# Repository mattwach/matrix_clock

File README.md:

# matrix_clock
> "I DON’T EVEN SEE THE CODE ANYMORE" - The Matrix.  

Shown above is a clock that presents the current time on an 64x32 RGB LED
matrix.  The clock has other selectable modes, including a view that includes
the numbers:

and some other selectable views:

Although the images above give you a basic idea, they can't show you the
dynamic range of the LED or the visual impression of 200 FPS animations,

The project's firmware is designed to easily incorporate support for other
hardware configurations.  Included is a 8x8 "Dotstar" matrix version that was my
first version:

*This document* focuses on the newer 62x32-based model, which I prefer.  If you
want to learn more details on the 8x8 build, I have a separate document
for it [here](README_dotstar_8x8.md).

In the upcoming sections, I explain how I built the clock.  I also
explain how to modify the design in different ways.

# Parts List

You can of course modify the design to use different ones.  Prices are "at time
of writing":

   * Microcontroller: [Raspberry PI Pico ($4)](https://www.adafruit.com/product/4864)
   * [LED Matrix 62x32: ($30)](https://www.amazon.com/waveshare-Displaying-Animation-Adjustable-Brightness/dp/B0B3W1PFY6)
     Note there are many vendors of this display - I assume they have similar
     interfaces.
   * Clock: [DS3231-based RTC module ($4)](https://www.amazon.com/HiLetgo-AT24C32-Arduino-Without-Battery/dp/B00LX3V7F0).
     This part is optional-but-recommended. The firmware can be built to use the
     Pi Pico clock libraries but you will lose battery backup and the time
     will drift more. 
   * Buttons: I used [2 6mm push buttons for control (<$1)](https://www.amazon.com/WOWOONE-12x12x7-3-Tactile-Momentary-Assortment/dp/B08JLWTQ3C)
     and one 6x3 SMD button for optional reset capability.
   * Connectors:
     * I used one 8x2 2.54 pitch male pin header to interface the Pico PCB with
       the matrix (using the usually-included interface cable)
     * I used a 2x1 angled 2.54 pitch pin header for connecting the LED to the
       PCB.
     * I used a 3x1 angled 2.54 pitch pin header for connecting the buttons to
       the PCB
   * I used a 220uF capacitor to reduce 5V noise.  Somewhat larger or smaller
     values should also work fine.
   * Circuit board for assembling components.
     * There are many options.  I ended up ordering a PCB from
       http://oshpark.com for the main board because my PCB layout needs a
       two-layer board.  I could have wired it up on perf board, but the large
       number of pin connections would have make it difficult to get a clean
       result.
     * There is a separate PCB for the buttons.  This board is very simple so
       any build technique should be straight-forward.  I used my CNC
       machine to cut a board within an hour.  If you order a main board, you
       might opt to bundle the button pcb with the order. 

Optional:

The LED display can pull over 3A if all LEDs are set to white.  The firmware I
wrote never does this and needs about 100-300 mA for most of the modes
(as-measured with a multimeter).  Thus I'm using the Pi Pico's VDD pin, which is
directly connected to USB power.  This connection should be limited to 500 mA or
less, thus I added the following electronic components to enforce the current
limit:

   * NCP380 current limiting IC
   * Two additional 1uf capacitors for stability.  I am using SMD but ceramic
     through-hole are also an option.

My hardware has this current protection but it has never activated outside of
testing thus one might argue that it's not needed.  If you plan to make your own
display modes, I suggest including the protection.

# Reading the clock

How can the clock be read when no numbers are shown?  By noting the colors and
speed of the particles.  Here is my color mapping for each number, as shown in
the time setting interface:

> Colors are defined in [src/colors.c](src/colors.c) if you would like to edit
> them.

# Feature Overview

This is a quick tour of the built in-features

## Power On

When you plug in the clock via any USB power source you will get a matrix clock
display that indicates the current time as-reported by the RTC clock hardware.

## Setting the Time

The clock has two buttons on it's side: "set" and "increment". Pressing "set"
goes into time change mode where you can use "set" and "increment" to change
each time digit.

> You can also set the clock via the USB connection.

## Changing the Display Mode

If you press the "increment" button while the matrix is showing, the clock will
cycle through display modes.  Currently defined modes include:

* **Simple** Shows the time with no animations.  The color of the time
  changes throughout the day to approximate a sunrise/daytime/sunset color
  temperature.
* **Matrix With Numbers** The default
* **Matrix Only** For those who want a challenge
* **Bounce** Particles bounce around the numbers. 
* **Number Cascade** Digits fall from the top of the display to the bottom.  The
  size and speed of the digit represent the place in the time (hours vs
  minutes).
* **Waveform** Waveforms progress from the bottom of the display to the top at
  different speeds based on the time digit.
* **Drops** A water droplet effect appears behind the numbers.
* **Off -**  Useful if you want a darkened room.

Each display mode uses color as described earlier to accent the current time.

## Console Configuration

If you plug the clock into a computer, you can run a terminal emulator program
to access many additional settings.  In Linux, I use the "minicom" terminal
emulator and my command looks like this:

```bash
minicom -b 115200 -P /dev/ttyUSB0
```

> The serial device (`/dev/ttyUSB0`) can vary between computers and operating
> systems. 

Once started, you will see something like this:

> By default, `minicom` turns on local echo, making my typed characters appear
> twice.  `minicom` allows this to be turned off with `ctrl-a e`.

Type `help` or `?` for help.

# Build Instructions

## Electronics

Here is the schematic for the 64x32 version:

Here is a description on major components and their purpose:

  - **Pi Pico**: This is the main controller
  - **RTC (Real Time Clock, Optional)**: This provides time to the Pico via an I2C connection.
    You could use alternate clock hardware as described in a later section.  In
    terms of the I2C connection, note that the RTC clock is powered by 3.3V
    instead of the specified 5V.  This is the easiest way to make the clock
    compatible with the 3.3V maximum voltage of the PI Pico.  If your RTC really
    does need 5V, there are solutions but the details are not the focus of this
    document.  Thus I suggest doing a Google search for "3.3 to 5V I2C" to learn
    more.
  - **64x32 matrix**: This is also a 5V part and is connected to the 5V VDD of the
    Pico, allowing ~500mA to be safely consumed by the panel.  The Pico is
    directly connected and will deliver 0-3.3V *signals* to the panel.  Unlike
    I2C for the RTC clock, the LED pins are high impedance inputs with no pullup
    thus there is no hardware risk in connecting them directly to the Pico.  The
    main risk is that the LED panel will not accept 3.3V as a legitimate "high"
    signal and thus it wont work.  For my panel 3.3V was accepted without a
    problem thus no level converters were needed.  I suspect this is the common
    scenario with these panels.
  - **100 uF-470 uF capacitor**.  The actual value is not important other than
    "big".  The purpose of the capacitor is to support the power requirements of
    the LED, which can be a "noisy" load, needing near zero current one moment
    and several hundred mA the next.
  - **Buttons**.  Select, increment and reset as described earlier.
  - **NCP380 current limiting chip (optional)**.  This chip provides insurance for
    the case where you one day decide to change the firmware to light up many
    LEDs and draw too much current.  If you really want to do support high
    current draw, you'll need to rework the power design so that the LED panel
    can be directly powered from a capable (3A+) source instead of VDD on the
    Pico.
    
> VDD on the Pico is a direct passthrough to the USB power so it's the
> USB regulator (wall adapter or computer) and the PCB traces of the Pico that are
> the main power bottlenecks.

> If you don't us use the NCP380, simply connect the Pico VDD pin directly to the LED.
> Keep the 100u capacitor for noise purposes.

In terms of layout, here is the KiCAD layout for the schematic above (with
ground plane hidden):

and here is a photo of the completed PCB.  Note that the capacitor can't be seen
because it is on the backside of the board:

As for the buttons, here is the simple KiCAD layout:

and the finished board that I cut out with my CNC machine (just using a perf
board would also work fine):

## Firmware

> TLDR: If you don't want to build the firmware (`matrix_clock_led_64x32.uf2`) 
yourself, I have a couple of precompiled versions under the
[firmware](firmware) directory.

Source files (written in C) are  provided in the [src/](src) directory.  If you
have never built PI Pico firmware before, run through the official [Getting
started with the Raspberry Pi
PICO](https://datasheets.raspberrypi.com/pico/getting-started-with-pico.pdf)
documentation first to get the needed tools up-and-running on your system.

The instructions for building the clock firmware are the same as the guide
linked above, but I created a small/simple [bootstrap.sh](src/bootstrap.sh)
script to lessen the number to needed steps:

```bash
./bootstrap.sh 
cd build/
make -j
```

I encourage you to view the contents of [bootstrap.sh](src/bootstrap.sh)
  yourself instead of blindly running it.  You'll see something like this:

```bash
$ cat bootstrap.sh 
#!/bin/bash

if [ ! -f pico_uart_console/CMakeLists.txt ]; then
  git submodule init
  git submodule update
fi

rm -rf build
mkdir build
cd build
cmake ..
```

> If building under Windows, you may opt to run the DOS-equivalent commands
> contained within `bootstrap.sh` manually.  The good news is that there
> are only a few commands to run.

The two major things done here are getting some dependencies (git submodules)
and setting up a new build environment under `build/`

If all went well above, you will have a `src/build/matrix_clock.uf2` file
available to load onto a PI Pico.  Note that
`firmware/matrix_clock_led_64x32.uf2` will not be changed.

# Hardware build

The hardware build is fairly minimalistic, solving the given problems:

  * Securing the PI Pico, RTC hardware and buttons at the bottom of the panel
  * Keeping the connection cables constrained so the clock can mount flat on a
    wall
  * Providing a wall mount

I solved all of these problem by creating a couple of 3D models and printing them out.
I used OpenSCAD for the modeling.

This model is located at
[case/led_matrix_64x32/led_matrix_64x32.scad](case/led_matrix_64x32/led_matrix_64x32.scad).
It can be modified with any text editor and viewed in the free
[OpenSCAD](http://openscad.org) software.

If you don't want to mess around with OpenSCAD, I also have the models available
for direct download at
[case/led_matrix_64x32/export](case/led_matrix_64x32/export).  These are .3mf
files (the successor to .stl format) that most modern slicer programs can
directly load.

To assemble, I used M2 bolts to attach the buttons to the bottom, 6mm long I
think but something in that area should be fine.  I used M3 bolts (around
12-16mm) to attach the 3D printed parts to the led matrix.

The PCB settles into a custom slot in the bottom 3d part (see the grooves in the
red image above) and is held in place with no bolts required, just make sure
it's in the proper position before tightening the frame bolts.

The hex matrixes on the back hold the power and led interface cables within the
unit so that it will mount flush on the wall.  A guide and slot is provided for
wall hanging the unit.

# Customization Guide

This part of the documentation points you in the right direction if you want to
modify the project.  This entire section should be consider optional and more
advanced than others.

## Using Different LED Hardware

The file [src/led_matrix.h](src/led_matrix.h), contains the interface your
hardware driver will be called with.
[src/led_matrix_62x32.c](src/led_matrix_64x32.c) implements it for the 64x32 LED
hardware.  There is also a [src/led_matrix_dotstar.c](src/led_matrix_dotstar.c)
file which is used *instead* when building the dotstar version.  To add
additional hardware support, create a new `.c` file (for example
`src/led_matrix_neopixel.c`) and change [src/CMakeLists.txt](src/CMakeLists.txt)
to point to your new file.c`.  The main function you'll be implementing is:

```c
#define LED_MATRIX_WIDTH 8
#define LED_MATRIX_HEIGHT 8

// render the matrix.
// data is of the form 0xIIRRGGBB where
// II -> Intensity (brightness)
// RR -> Red
// GG -> Green
// BB -> Blue
//
// Values are 0-255
// format is horizontal rows.  The first pixel
// sent is the southwest corner of the matrix.
void led_matrix_render(uint32_t* data);
```

Again, look at [src/led_matrix_dotstar.c](src/led_matrix_dotstar.c) for a
straight-forward implementation of `led_matrix_render`.

## Using Different Clock Hardware

Instead of an RTC, you might want to go with a radio-based clock, a GPS clock,
or [keeping the time with the Pi
Pico](https://raspberrypi.github.io/pico-sdk-doxygen/group__hardware__rtc.html).

> The PICO SDK provides time functions but you'll lose battery backup and
accuracy is not as good as a real RTC.

[src/clock.h](src/clock.h) gives the interface:

```c
// gets the current time in HHMM format (0000 - 2359)
// For example, if 1354 is returned, the time is 13:54 (or
// 1:34 PM if you prefer)
uint16_t clock_get_time();

// Sets the time.  For example: time_hhmm = 1234 would set the
// time to 12:34.  Note that 24h time is always used so 1234
// is 12:34 PM and 0034 is 12:34 AM.
void clock_set_time(uint16_t time_hhmm);
```

and [src/clock_ds3231.c](src/clock_d23231.c) gives a concrete implementation for
the RTC module.  The file [src/clock_pico_internal.c](src/clock_pico_internal.c)
provides an implementation that does not need RTC hardware.  It can be selected
in [src/CMakeLists.txt](src/CMakeLists.txt).

## Adding / Changing Display Modes

There are two files and one directory to consider.  The first file is
[src/clock_render.c](src/clock_render.c).  Specifically, this section:

```c
  struct DisplayMode display_modes[] = {
    {"matrix_with_numbers", matrix_with_numbers_render},  // This entry will be the default power-on mode
    {"matrix", matrix_render},
    {"bounce", bounce_render},
    {"number_cascade", number_cascade_hires_render},
    {"waveform", waveform_render},
    {"drops", drops_render},
    {"off", blank_render},  // always put this entry at the end of the list
  };
```

This section lists the display modes, names them and provides a function pointer
to each one.  If you were to remove a line from this array, or reorder the
lines, you would see the corresponding change when you build/load new firmware.
In order for the function pointers to have any meaning, you'll need to include
the corresponding files:

```c
#include "render/matrix_with_numbers.h"
#include "render/matrix.h"
#include "render/bounce.h"
...
```

Note that, by convention, all rendering functions are defined in the
[src/render](src/render) directory.  Here is an example
[src/render/blank.c](src/render/blank.c):

```c
void blank_render(
    uint32_t* led,
    uint32_t frame_index,
    uint16_t time_hhmm,
    const struct ClockSettings* settings) {
  memset(
    led,
    0,
    LED_MATRIX_WIDTH * LED_MATRIX_HEIGHT * sizeof(uint32_t));
}
```

This simple function simply clears the `led` array to zero which effectively
turns off the display.

The `time_hhmm` provides the time as an integer.  For example, 1:45 AM would be
represented as `0145` and 1:45 PM would be represented as `1345`.

The `frame_index` parameter can be useful for initialization.  It is always set
to `0` when the display mode is made active.

The `settings` structure has several potentially-useful fields but especially
useful is getting the user preference for LED brightness:

```c
  const uint8_t br = brightness_step_to_brightness(settings);
```

This value (0-255), would then be used as a baseline brightness when turning on
LEDs in `led`

## Changing the Console

The file `src/clock_settings.c` contains all of the commands available to the
USB shell.  Adding your own is straight-forward but I suggest skimming through
https://github.com/mattwach/pico_uart_console to get up-to-speed on how the
console works first.

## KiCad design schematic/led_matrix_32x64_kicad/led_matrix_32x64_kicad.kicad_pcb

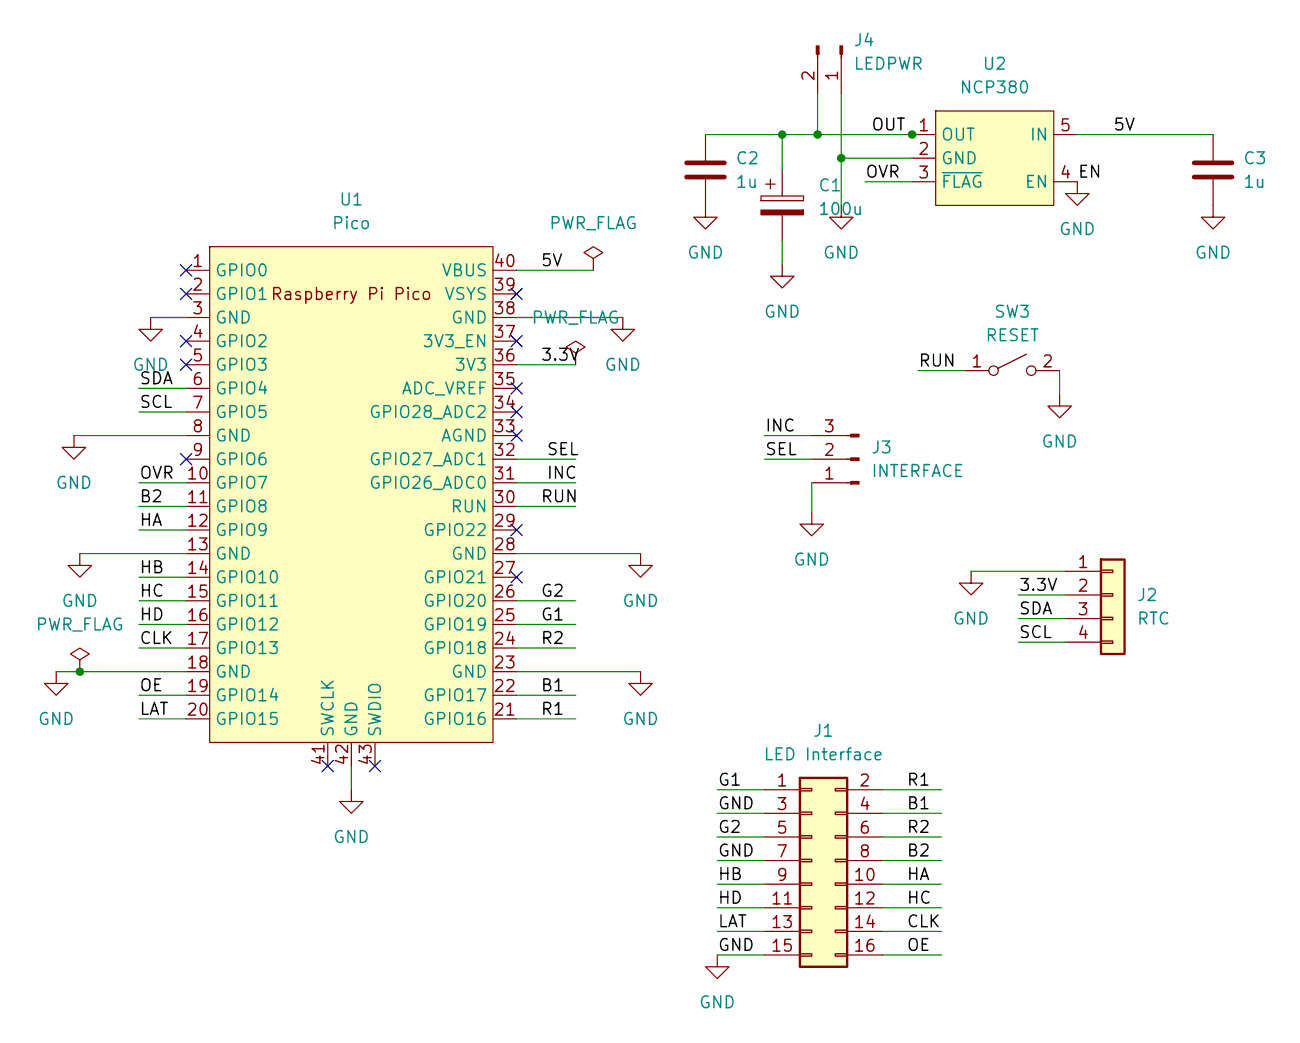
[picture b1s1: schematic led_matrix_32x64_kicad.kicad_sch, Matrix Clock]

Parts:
C1: 100u; CP_Radial_D6.3mm_P2.50mm
C2, C3: 1u; C_0805_2012Metric_Pad1.18x1.45mm_HandSolder
J1: LED Interface; PinHeader_2x08_P2.54mm_Vertical
J2: RTC; PinHeader_1x04_P2.54mm_Vertical
J3: INTERFACE; PinHeader_1x03_P2.54mm_Horizontal
J4: LEDPWR; PinHeader_1x02_P2.54mm_Horizontal
SW3: RESET; SMD_Button_6mm_3_5mm
U1: Pico; RPi_Pico_SMD_TH
U2: NCP380; TSOP-5_1.65x3.05mm_P0.95mm

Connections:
/3.3V: J2.2, U1.36 (3V3)
/5V: C3.1, U1.40 (VBUS), U2.5 (IN)
/B1: J1.4, U1.22 (GPIO17)
/B2: J1.8, U1.11 (GPIO8)
/CLK: J1.14, U1.17 (GPIO13)
/G1: J1.1, U1.25 (GPIO19)
/G2: J1.5, U1.26 (GPIO20)
/HA: J1.10, U1.12 (GPIO9)
/HB: J1.9, U1.14 (GPIO10)
/HC: J1.12, U1.15 (GPIO11)
/HD: J1.11, U1.16 (GPIO12)
/INC: J3.3, U1.31 (GPIO26_ADC0)
/LAT: J1.13, U1.20 (GPIO15)
/OE: J1.16, U1.19 (GPIO14)
/OUT: C1.1, C2.1, J4.2, U2.1 (OUT)
/OVR: U1.10 (GPIO7), U2.3 (~FLAG)
/R1: J1.2, U1.21 (GPIO16)
/R2: J1.6, U1.24 (GPIO18)
/RUN: SW3.1 (A), U1.30 (RUN)
/SCL: J2.4, U1.7 (GPIO5)
/SDA: J2.3, U1.6 (GPIO4)
/SEL: J3.2, U1.32 (GPIO27_ADC1)

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
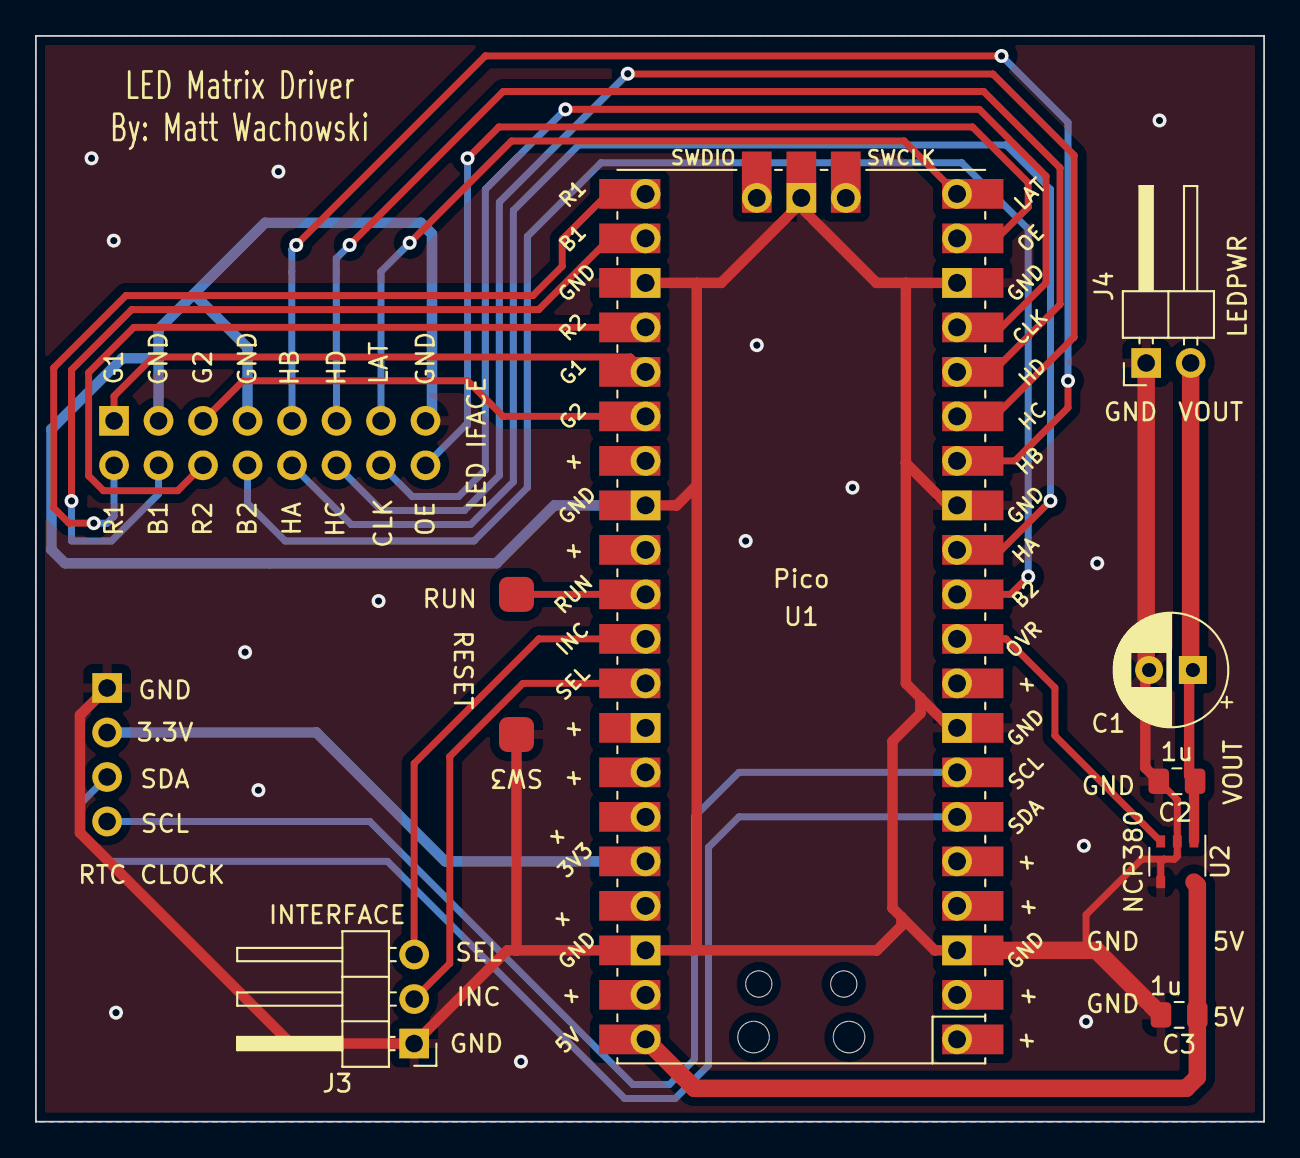
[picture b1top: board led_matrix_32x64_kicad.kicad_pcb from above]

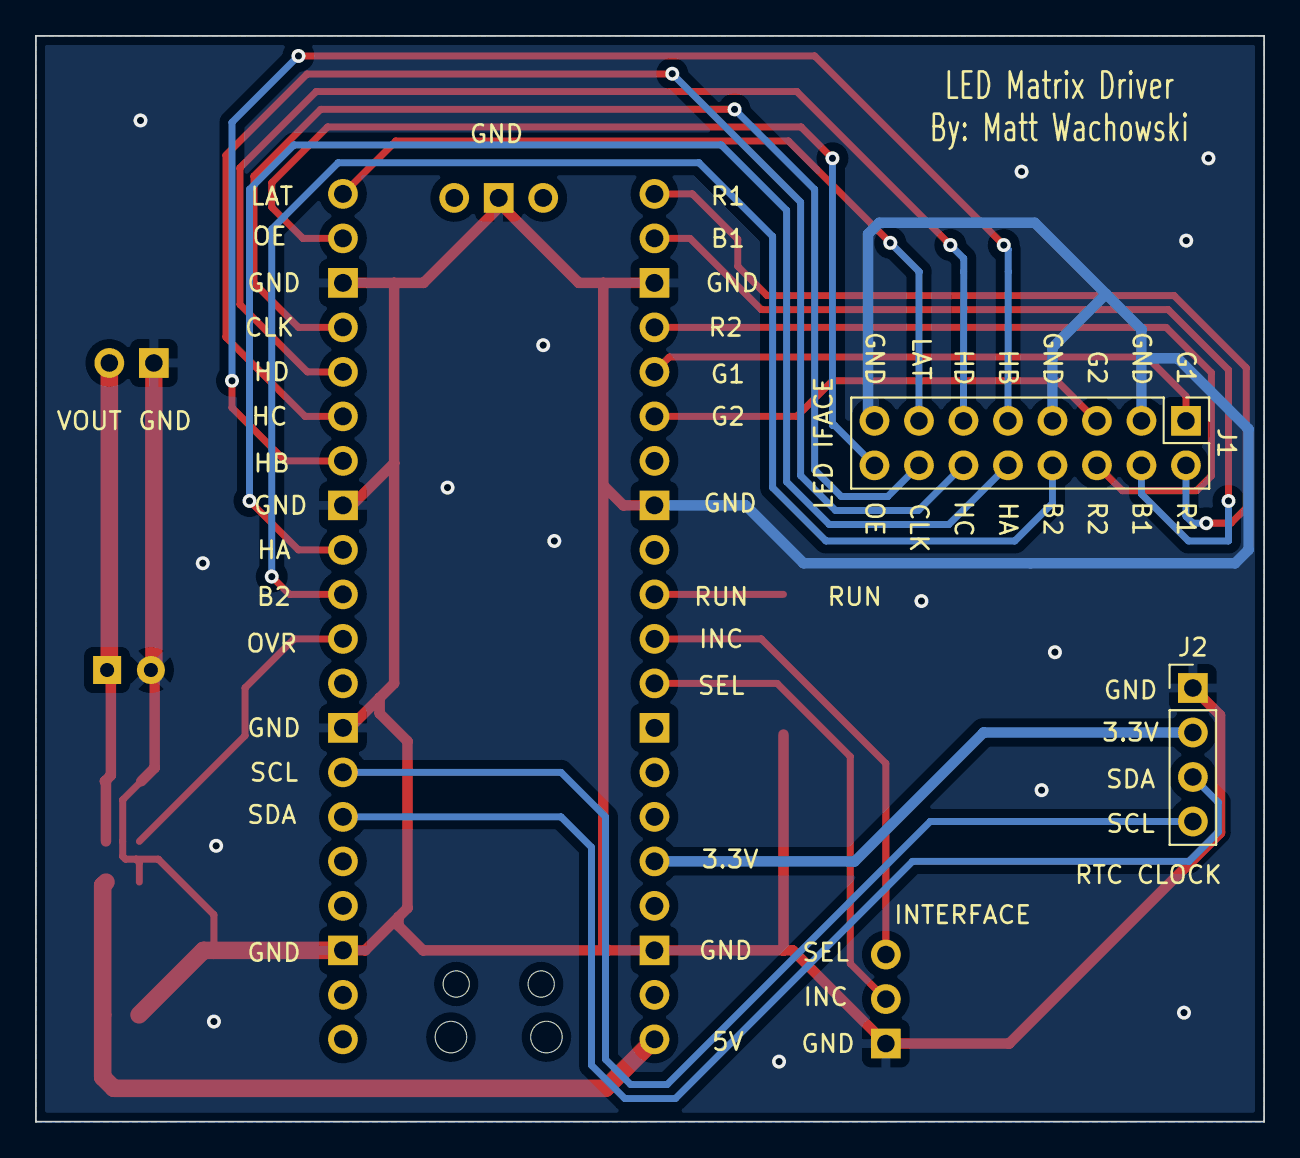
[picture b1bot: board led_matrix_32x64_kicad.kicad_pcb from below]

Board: 2 copper layers, 70.1 x 62.0 mm, 10 parts (2 on the bottom side), 23 nets.

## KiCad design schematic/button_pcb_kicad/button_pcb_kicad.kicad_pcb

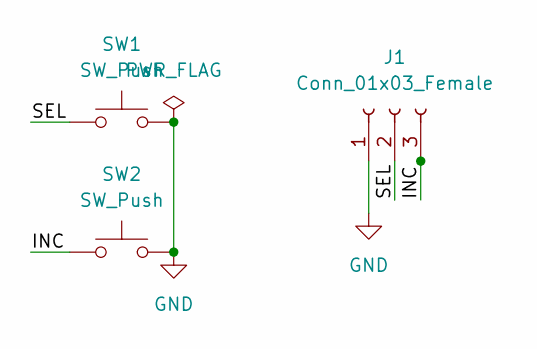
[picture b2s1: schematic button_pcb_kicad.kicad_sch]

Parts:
J1: Conn_01x03_Female; SMD_Pad_1x03_2mm
SW1, SW2: SW_Push; SW_PUSH_6mm_H4.3mm

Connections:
/INC: J1.3, SW2.1
/SEL: J1.2, SW1.1
GND: J1.1, SW1.2, SW2.2

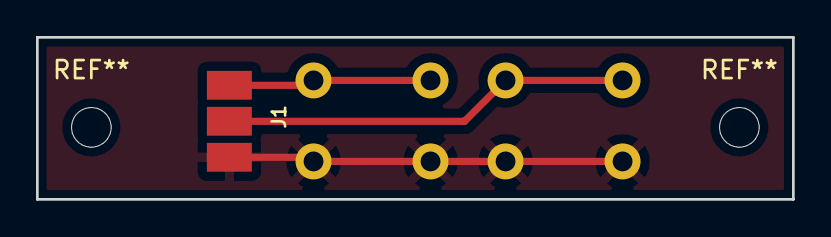
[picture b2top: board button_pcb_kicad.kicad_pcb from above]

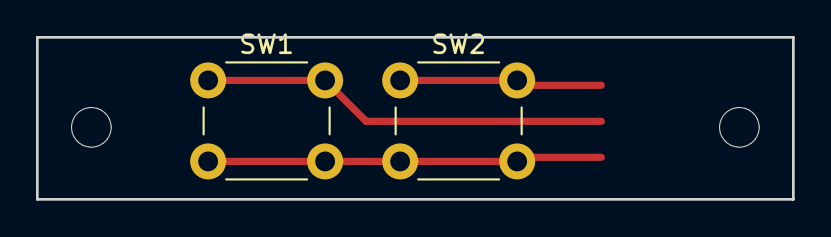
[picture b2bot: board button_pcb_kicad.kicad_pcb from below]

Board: 2 copper layers, 42.0 x 9.0 mm, 3 parts (2 on the bottom side), 3 nets.

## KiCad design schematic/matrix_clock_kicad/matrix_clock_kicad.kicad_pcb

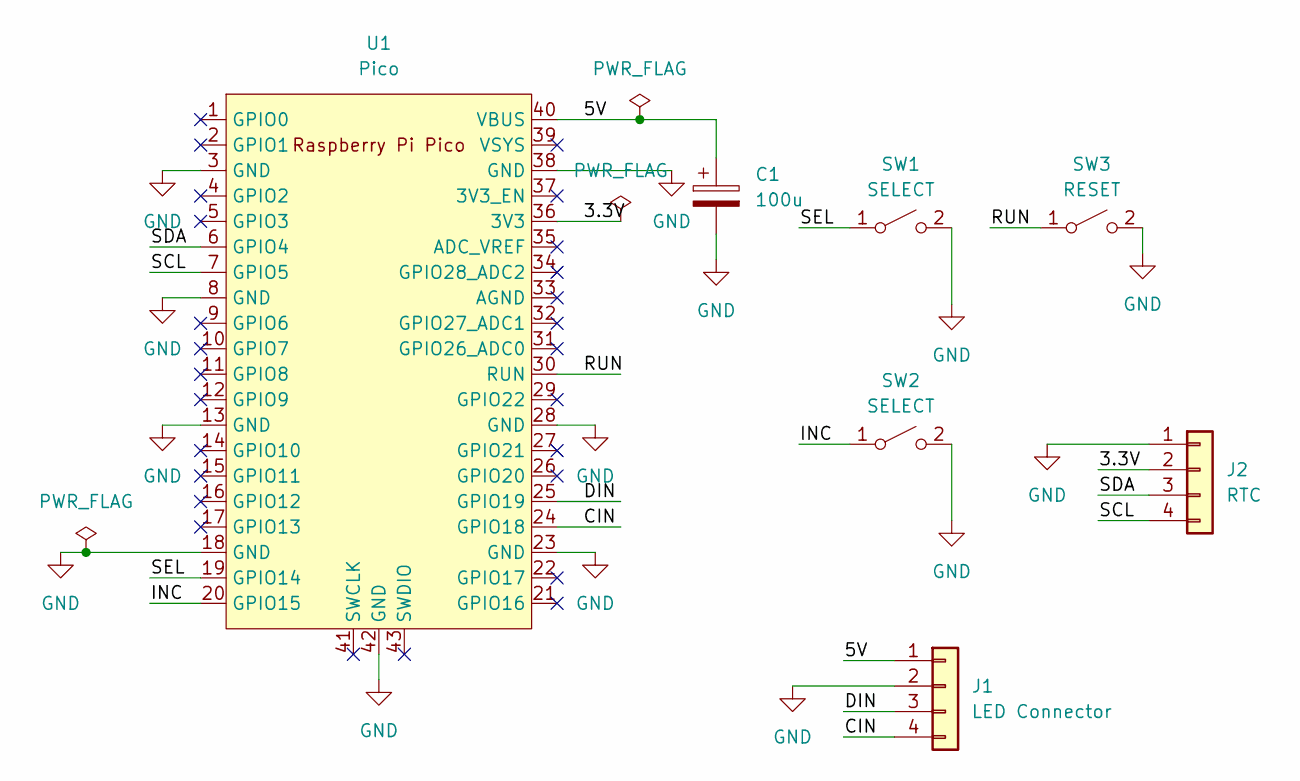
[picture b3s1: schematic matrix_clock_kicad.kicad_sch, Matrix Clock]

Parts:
C1: 100u; CP_Radial_D6.3mm_P2.50mm
J1: LED Connector; PinHeader_1x04_P2.54mm_Vertical
J2: RTC; PinHeader_1x04_P2.54mm_Vertical
SW1, SW2: SELECT; SW_PUSH-12mm
SW3: RESET; SMD_Button_6mm_3_5mm
U1: Pico; RPi_Pico_SMD_TH

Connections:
/3.3V: J2.2, U1.36 (3V3)
/5V: C1.1, J1.1, U1.40 (VBUS)
/CIN: J1.4, U1.24 (GPIO18)
/DIN: J1.3, U1.25 (GPIO19)
/INC: SW2.1 (A), U1.20 (GPIO15)
/RUN: SW3.1 (A), U1.30 (RUN)
/SCL: J2.4, U1.7 (GPIO5)
/SDA: J2.3, U1.6 (GPIO4)
/SEL: SW1.1 (A), U1.19 (GPIO14)
GND: C1.2, J1.2, J2.1, SW1.2 (B), SW2.2 (B), SW3.2 (B), U1.3 (GND), U1.8 (GND), U1.13 (GND), U1.18 (GND), U1.23 (GND), U1.28 (GND), U1.38 (GND), U1.42 (GND)

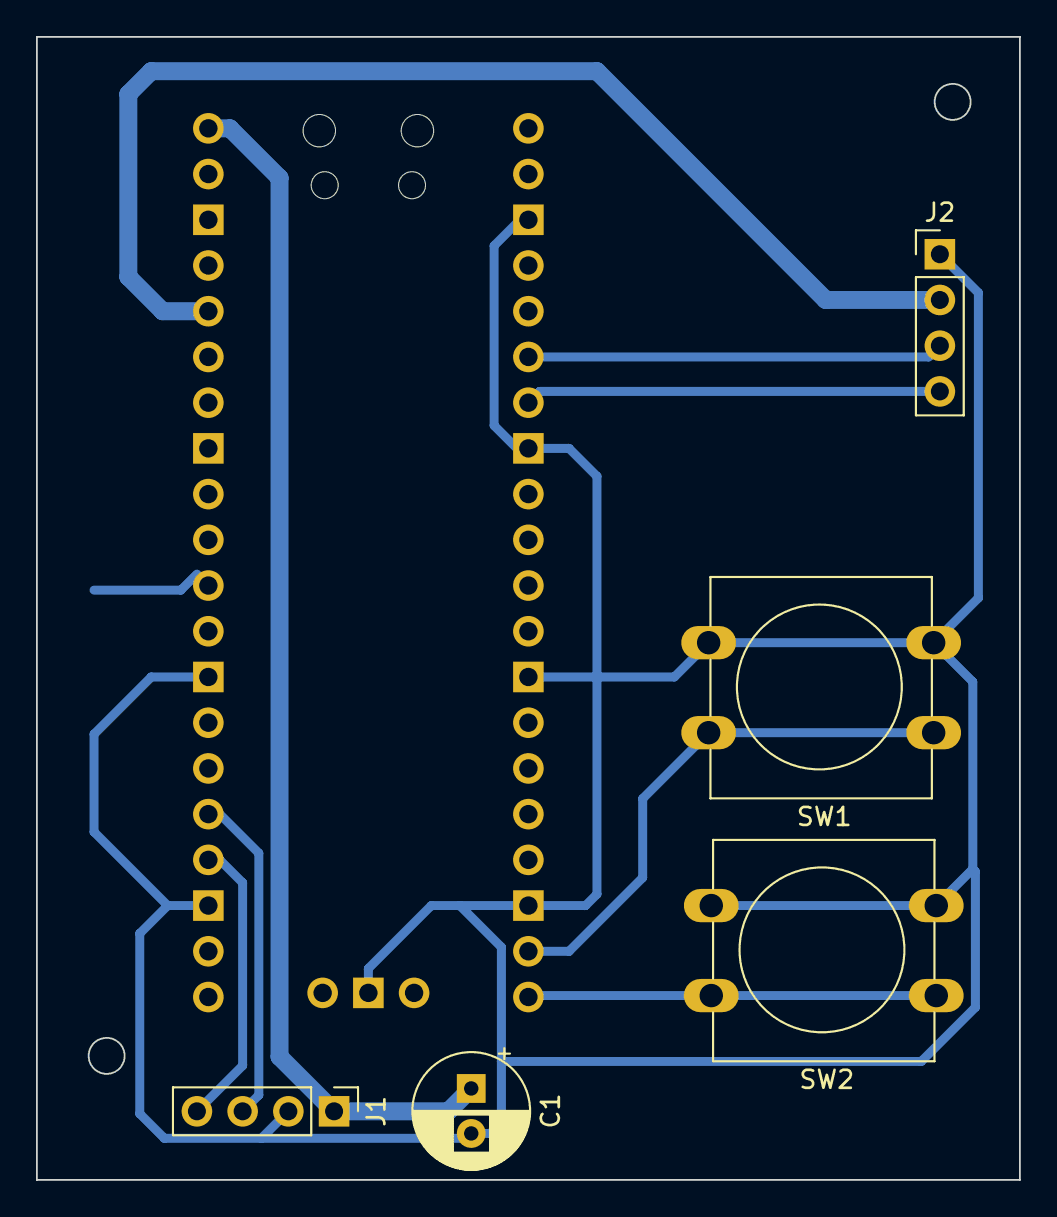
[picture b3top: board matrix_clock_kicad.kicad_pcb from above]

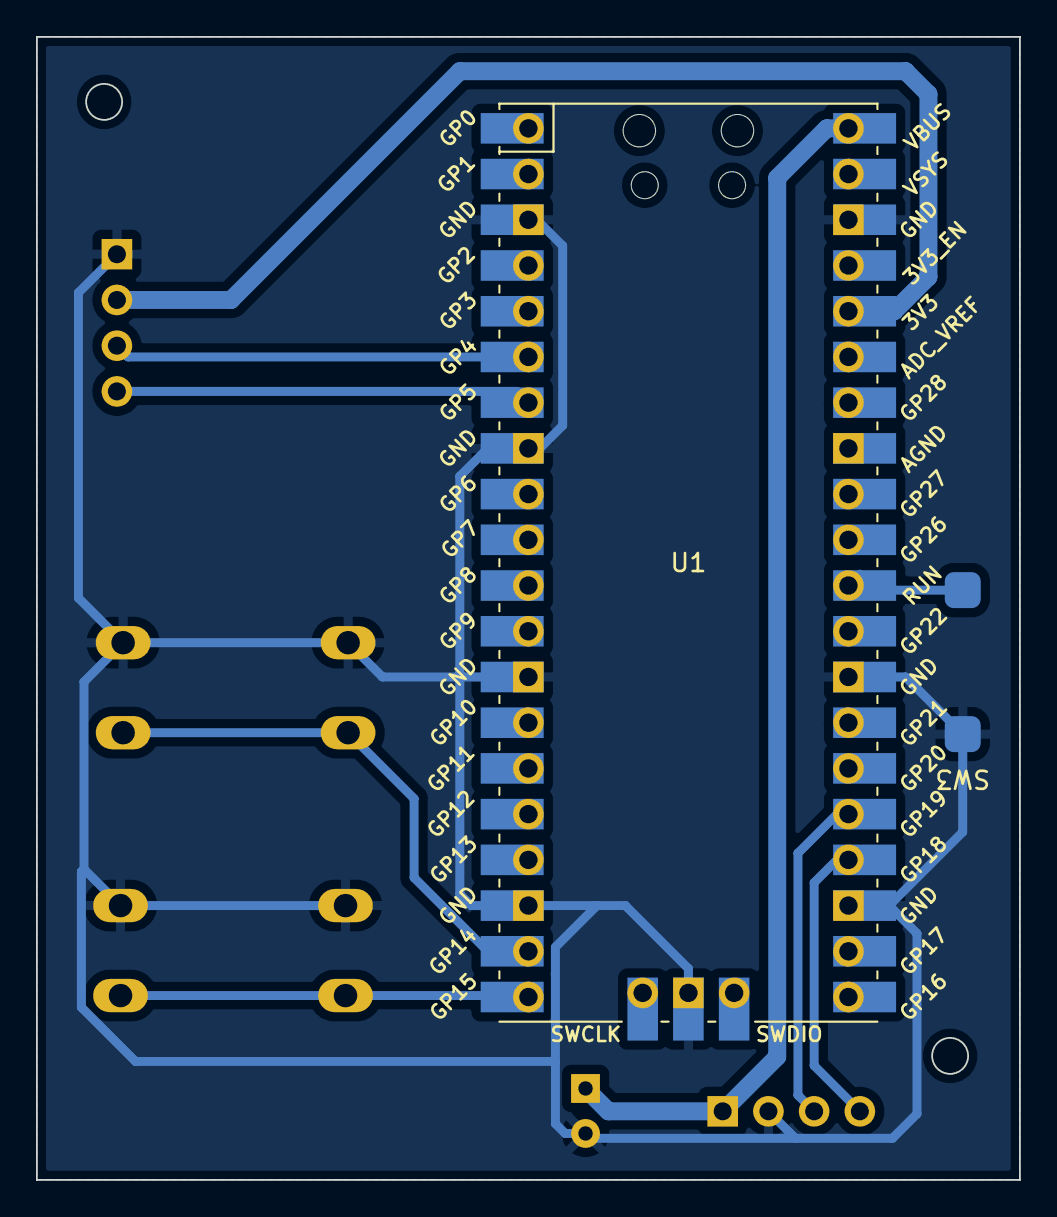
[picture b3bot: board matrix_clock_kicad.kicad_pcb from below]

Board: 2 copper layers, 54.6 x 63.5 mm, 7 parts (2 on the bottom side), 10 nets.

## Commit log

2022-12-07 Snapshot from my pricate repro
2022-12-07 Added pico_uart_console
2022-12-07 Replaced logging with console
2022-12-07 Moved prompt generation to a separate function
2022-12-08 Disabled VT100 debug mode.
2022-12-08 Drafted clock settings. Implemented brightness.
2022-12-08 Fixed flash save bug. Fixed brightness command args.
2022-12-08 Started implementing other display modes.
    Does not compile yet.
2022-12-08 Added new display modes. Untested.
2022-12-08 Pulling in latest version
2022-12-09 Switch back to 8-bit brightness and improved overlays.
2022-12-09 Added CLOCK_SETTINGS_VERSION
2022-12-09 Moved ClockSettings into clock_settings.c
2022-12-09 Added set_time command
2022-12-09 Add frame_index_delta so that clock number are always shown on change.
2022-12-09 Added startup_display_mode setting.
2022-12-09 Added sleep_time and wake_time
2022-12-09 save setting on appropriate commands
2022-12-09 Started kicad schematic
2022-12-09 Removed backups folder
2022-12-10 update pico_uart_console
2022-12-11 Completed PCB layout
2022-12-11 Added gerber and drill exports.
    Some of these will likely need to be mirrored in flatcam.
2022-12-11 Saved some plot options
2022-12-11 Initial flatcam project
2022-12-11 Added and mirrored gerber and drills. Fixed drills.
2022-12-11 Generated cu gcode
2022-12-11 Added edge cuts gcode
2022-12-11 Added drilling gcode
2022-12-11 Removed M0 gcode
2022-12-12 Removed unneeded drill holes for pi pico
2022-12-14 Exported step file
2022-12-14 Started assembled board
2022-12-14 Splitting up clock_render. Step 1: create render/matrix.h
2022-12-14 Splitting up clock_render. Step 2: create render/blank.h
2022-12-14 Splitting up clock_render. Step 2: create render/guide.h
2022-12-14 Splitting up clock_render. Step 2: create render/numbers.h
2022-12-14 forgot to add numbers files to last commit
2022-12-14 Refactor clock_render.c to leverage structured calling convention.
2022-12-14 Added pi pico
2022-12-15 Added RTC
2022-12-15 Added led matrix header.
2022-12-15 Added interface buttons
2022-12-15 added reset button
2022-12-15 Removed pin header from RTC to save on vertical space.
2022-12-15 Started scad file for the main case
2022-12-15 Don't include button caps.
    I dont have the correct color, they are not the right dimensions and
    the real PSB has slanted bases due to contruction.
2022-12-15 Implemented base_shell
2022-12-15 Added mounting posts.
2022-12-15 Dropped function pointer table because there are only expected to be two cases
2022-12-15 Added comments throoughtout the project
2022-12-16 Added boot and reset access holes
2022-12-16 Added led_matrix
2022-12-16 Startig to gravitate toward a vertical design.
2022-12-16 Added usb access hole
2022-12-16 Resized case a bit
2022-12-16 wworking on matrix mounting bars and somethig got messed up. Snapshotting so I can step through undos
2022-12-16 Added matrix mounting bars
2022-12-17 Switched matrix mount to minimal post.
    I *think* I want the light leak but well see.
2022-12-17 Added top cover
2022-12-17 Added button pegs
2022-12-17 Updated buttons to make them smaller and have fewer parts
2022-12-17 Adjusted button dimensions.
2022-12-17 Added a hole to the button peg backing plate.
2022-12-18 Worked on documentation.
2022-12-18 Added 3mf export files
2022-12-18 Added prusa slicer project for reference.
2022-12-19 Fix type of check sleep time
2022-12-19 Changed the way that fonts are drawn so that it's wasy to make new ones.
2022-12-19 Removed guide, and numbers rendering, added cascade.
    The 3D printed enclosure makes guide too fuzzy to be usable
    I never liked the way that guide worked.
    Hoping to make some new visulizations that are more appealing.
2022-12-19 Added number grid display modes.
2022-12-19 Changed font to use and API.
    This should be more robust against hardware chages that effect the matrix resolution.
2022-12-20 Tweak framerate and other timings.
2022-12-20 Changed merge to just overlay
2022-12-20 Trying to make particle selection more weighted.
2022-12-20 Remove event type validation code.
2022-12-20 Fixed rendering issue that were due to having the y orientation reversed.
2022-12-20 More messing with color values
2022-12-20 Remove 4x4 font and number grid.
    It was too hard to read.
2022-12-20 Added fade rendering
2022-12-20 Added debug functions.
2022-12-20 Bug fixes for fade renderer
2022-12-20 slightly darkened pink color
2022-12-20 slightly darkened brown color
2022-12-21 Fixed matrix render bug where initial colors were incorrect
2022-12-21 tweaked colors again
2022-12-24 Added some images and text to README
2022-12-26 Readme cleanup.
2022-12-26 Drafted README to completion.
2022-12-26 Made 3d printed case stand-alone
2022-12-26 Added notes on the 3d case
2022-12-26 Added missing openscad image
2022-12-28 Readme fixes
2022-12-30 Added firmware example
2022-12-30 Added pointer to firmware directory
2022-12-30 typo fix
2023-01-01 Typo fixes
2023-01-07 Added draft of 32x64 matrix.
    Not yet compiled or tested.
2023-01-07 Make close source and led matrix source variables
2023-01-07 Loved led matrix width and led matric height into cmake file.
2023-01-07 Added option to use internal clock
2023-01-07 Fixed compile issues with led_matrix_32x64
2023-01-07 Added DEFAULT_BRIGHTNESS_STEP, fixes to led_matrix
2023-01-07 Added missing | sign.
2023-01-07 Put select and increment GPIO selection in cmake file.
    My built-up hardware for the 32x64 matrix is using pins 14 and 15
    as part of driving the display.
2023-01-08 Well the 32x64 version is just way too cool looking
2023-01-08 Tuning the look
2023-01-08 Moving dotstart case into a sub folder
2023-01-08 Rename kicad schematic.
2023-01-08 Rename firnmware file
2023-01-08 Started schematic for led matrix 32x64
2023-01-08 Some tweaks that improve clock stability AND FPS.
2023-01-08 Fixed flash save hang.
    Multicore needs to be disabled, then properly reenabled.
2023-01-09 Stopped hangning of number fade on led_matrix module.
    Really this one should be disabled for this case.
2023-01-09 Clean up build to better support the older dotstar hardware.
2023-01-09 Remove binary grid.
    It's not useful for either usecase at this point in time.
2023-01-09 Switched number font to variable width
2023-01-09 Added display_mode shell command.
2023-01-09 Inverted font on y axis
2023-01-09 Added matrix_with_numbers overlay
2023-01-10 Added increment and select shell commands.
2023-01-10 Invert y on 32x64 display
2023-01-10 Fixed incorrect use of preprocessor to select matrix hardware.
2023-01-10 fixed 32x64 orientation
2023-01-10 Remove display_mode shell cmd. Fix time setting.
2023-01-10 Created a different set time rendering module for high res displays.
2023-01-13 Moved settings out of CMakeLists.txt
2023-01-13 Fixed typo in button config
2023-01-13 Starting the 32x64 matrix with a copy of the 8x8 dotstar.
2023-01-13 Mapped 32x64 pins to PICO
2023-01-13 Updated 32x64 schematic
2023-01-14 Started on PCB
2023-01-15 Snapshot before flipping the board
2023-01-15 New layout is getting closer
2023-01-15 More progress on PCB
2023-01-15 Moved RTC clock pins. Worked on labeling.
2023-01-15 Passing ERC and DRC checks
2023-01-15 Show all layewrs in kicad
2023-01-15 Added overcurrent detection
2023-01-22 Tuning the clock set
2023-01-22 The clock set is workable now.
2023-01-23 Masks
2023-01-23 Added additional glyphs to the one
2023-01-23 Added number_cascase_hires.
    Compiles but untested.
2023-01-23 Forgot to add the new files on the previous commit
2023-01-24 Got the number cascase looking pretty good.
2023-01-24 README upadtes for the 64x32
2023-01-24 Added 32x64 firmware build
2023-01-26 Decided to put 8x8 info in a separate document
2023-01-26 Separate older dotstar images
2023-01-26 Updates to remove the dotstar build from the README
2023-01-27 Added some gerber output settings
2023-01-27 Added solder paste layer
2023-01-27 added solder paste svg
2023-01-27 Added solder mask flatcam / cnc data
2023-01-27 updated flatcam data
2023-01-28 Icreased digit count
2023-01-28 Update clock source to use RTC
2023-01-28 project setting update
2023-01-28 Added schematic/pcb for pushbuttons.
2023-01-29 Added gcode for button pcb.
2023-01-29 Some settings for step export in kicad.
2023-01-30 Start of main_pcb model
2023-01-30 added rtc module
2023-01-30 Added led interface pins
2023-01-30 Added button pins
2023-01-30 Finished main pcb
2023-01-30 Added button_pcb
2023-01-30 Started main scad file.
2023-01-30 Placed main PCB
2023-01-30 Added right side bottom support
2023-01-30 Added back mesh
2023-01-30 added anti slide arm
2023-01-30 Repositioned button pcb
2023-01-30 added pcb cutout to bottom support
2023-01-30 added usb cutout
2023-01-30 Added button interface to bottom support
2023-01-30 Started top support
2023-01-30 Added hex grid to top support
2023-01-30 Finished top support
2023-01-30 Made hanging hold a bit larger
2023-01-30 Added exported 3d shapes
2023-01-31 update kicad schematin to tie MCP380 enable to ground
2023-01-31 Hacky fix to top side bolt offset problem
2023-01-31 Updated .3mf top support file with correct bolt offsets
2023-01-31 Fixed 62_32 typos
2023-01-31 Make the openscad project self-contained
2023-01-31 Rename 32x64 to 64x32
    The project was being inconsistent in choosing a name. This finalizes it on a name
    that people will more easily map to the hardware.
2023-01-31 Make matrix with numbers the default render mode
2023-01-31 Adding more text to readme file.
2023-02-01 Fixed orientation to reflect new power cable location
2023-02-01 Added a waveform rendering
2023-02-01 Added auto mode changing. Untested.
2023-02-02 Move increment display mode to a common function
2023-02-02 Improved wave mode
2023-02-02 Move the waves at different speeds
2023-02-02 Added more wave variation
2023-02-02 Added FPS metric.
    Tracked down and removed the FPS bottleneck. It was simply
    having random() in the clock_settings.c file - it
    wasn't even being called!
    Am I running into some behind-the-scenes limits? memory access patterns?
2023-02-02 Fixed the mode change calculation
2023-02-02 Looked at the time increment code and saw another bug.
2023-02-02 Cleaned up fps code, moving it to a different module.
2023-02-02 Fixed mode change minute settings bugs.
2023-02-02 Tie mode change time updates to the increment action.
    Ths allows manual updates to also reset the increment.
2023-02-02 Starting code for bounce.
2023-02-02 Draft of bounce render. Compiles but not tested.
2023-02-02 Boucing looks good
2023-02-02 Changed font to have a selectable color instead of white
2023-02-03 Added a distance code generator and output from the tool.
2023-02-03 Added weight calculations to distance_generator.py
2023-02-03 changed particle count
2023-02-03 Framework for glow render mode.
2023-02-03 moved tools dir
2023-02-03 Fixed bugs in distance_generator.py
2023-02-03 Untested draft of glow.c
2023-02-03 tuned the glow mode
2023-02-04 Updated built firmware
2023-02-04 Fixed initializtion bug with auto mode increment
2023-02-04 Fixed header name typo
2023-02-04 Updated dotstar firmware
2023-02-04 Updated led_64x32 firmware
2023-02-05 Readme updates and image adds.
2023-02-06 Rename glow->drops
2023-02-06 Added photo for matrix clock
2023-02-06 Readme updates.
2023-02-06 Enabled auto mode changes by default.
2023-02-08 Added console image.
2023-02-09 README updates
2023-02-10 README formatting and spelling fixes.
2023-02-11 Boleded last electronics step
2023-02-13 Rename dotstar matrix clock
2023-02-18 Image update
2026-04-21 Updated include to avoid compiler error via deprecation
2026-04-21 Start of a "simple" render that has no animation.
2026-04-21 Added some time-of-day color calculations to the simple render.
    It takes the Kelvin curve for a typical day, converted to RGB values
    and uses linear interpolation to determine a color given a time of
    day.
    Given that we have no date or GPS data, the result will not map
    outside conditions. That can be added later, it wanted.
2026-04-22 Updated firmware and readme to include simple rendering.
